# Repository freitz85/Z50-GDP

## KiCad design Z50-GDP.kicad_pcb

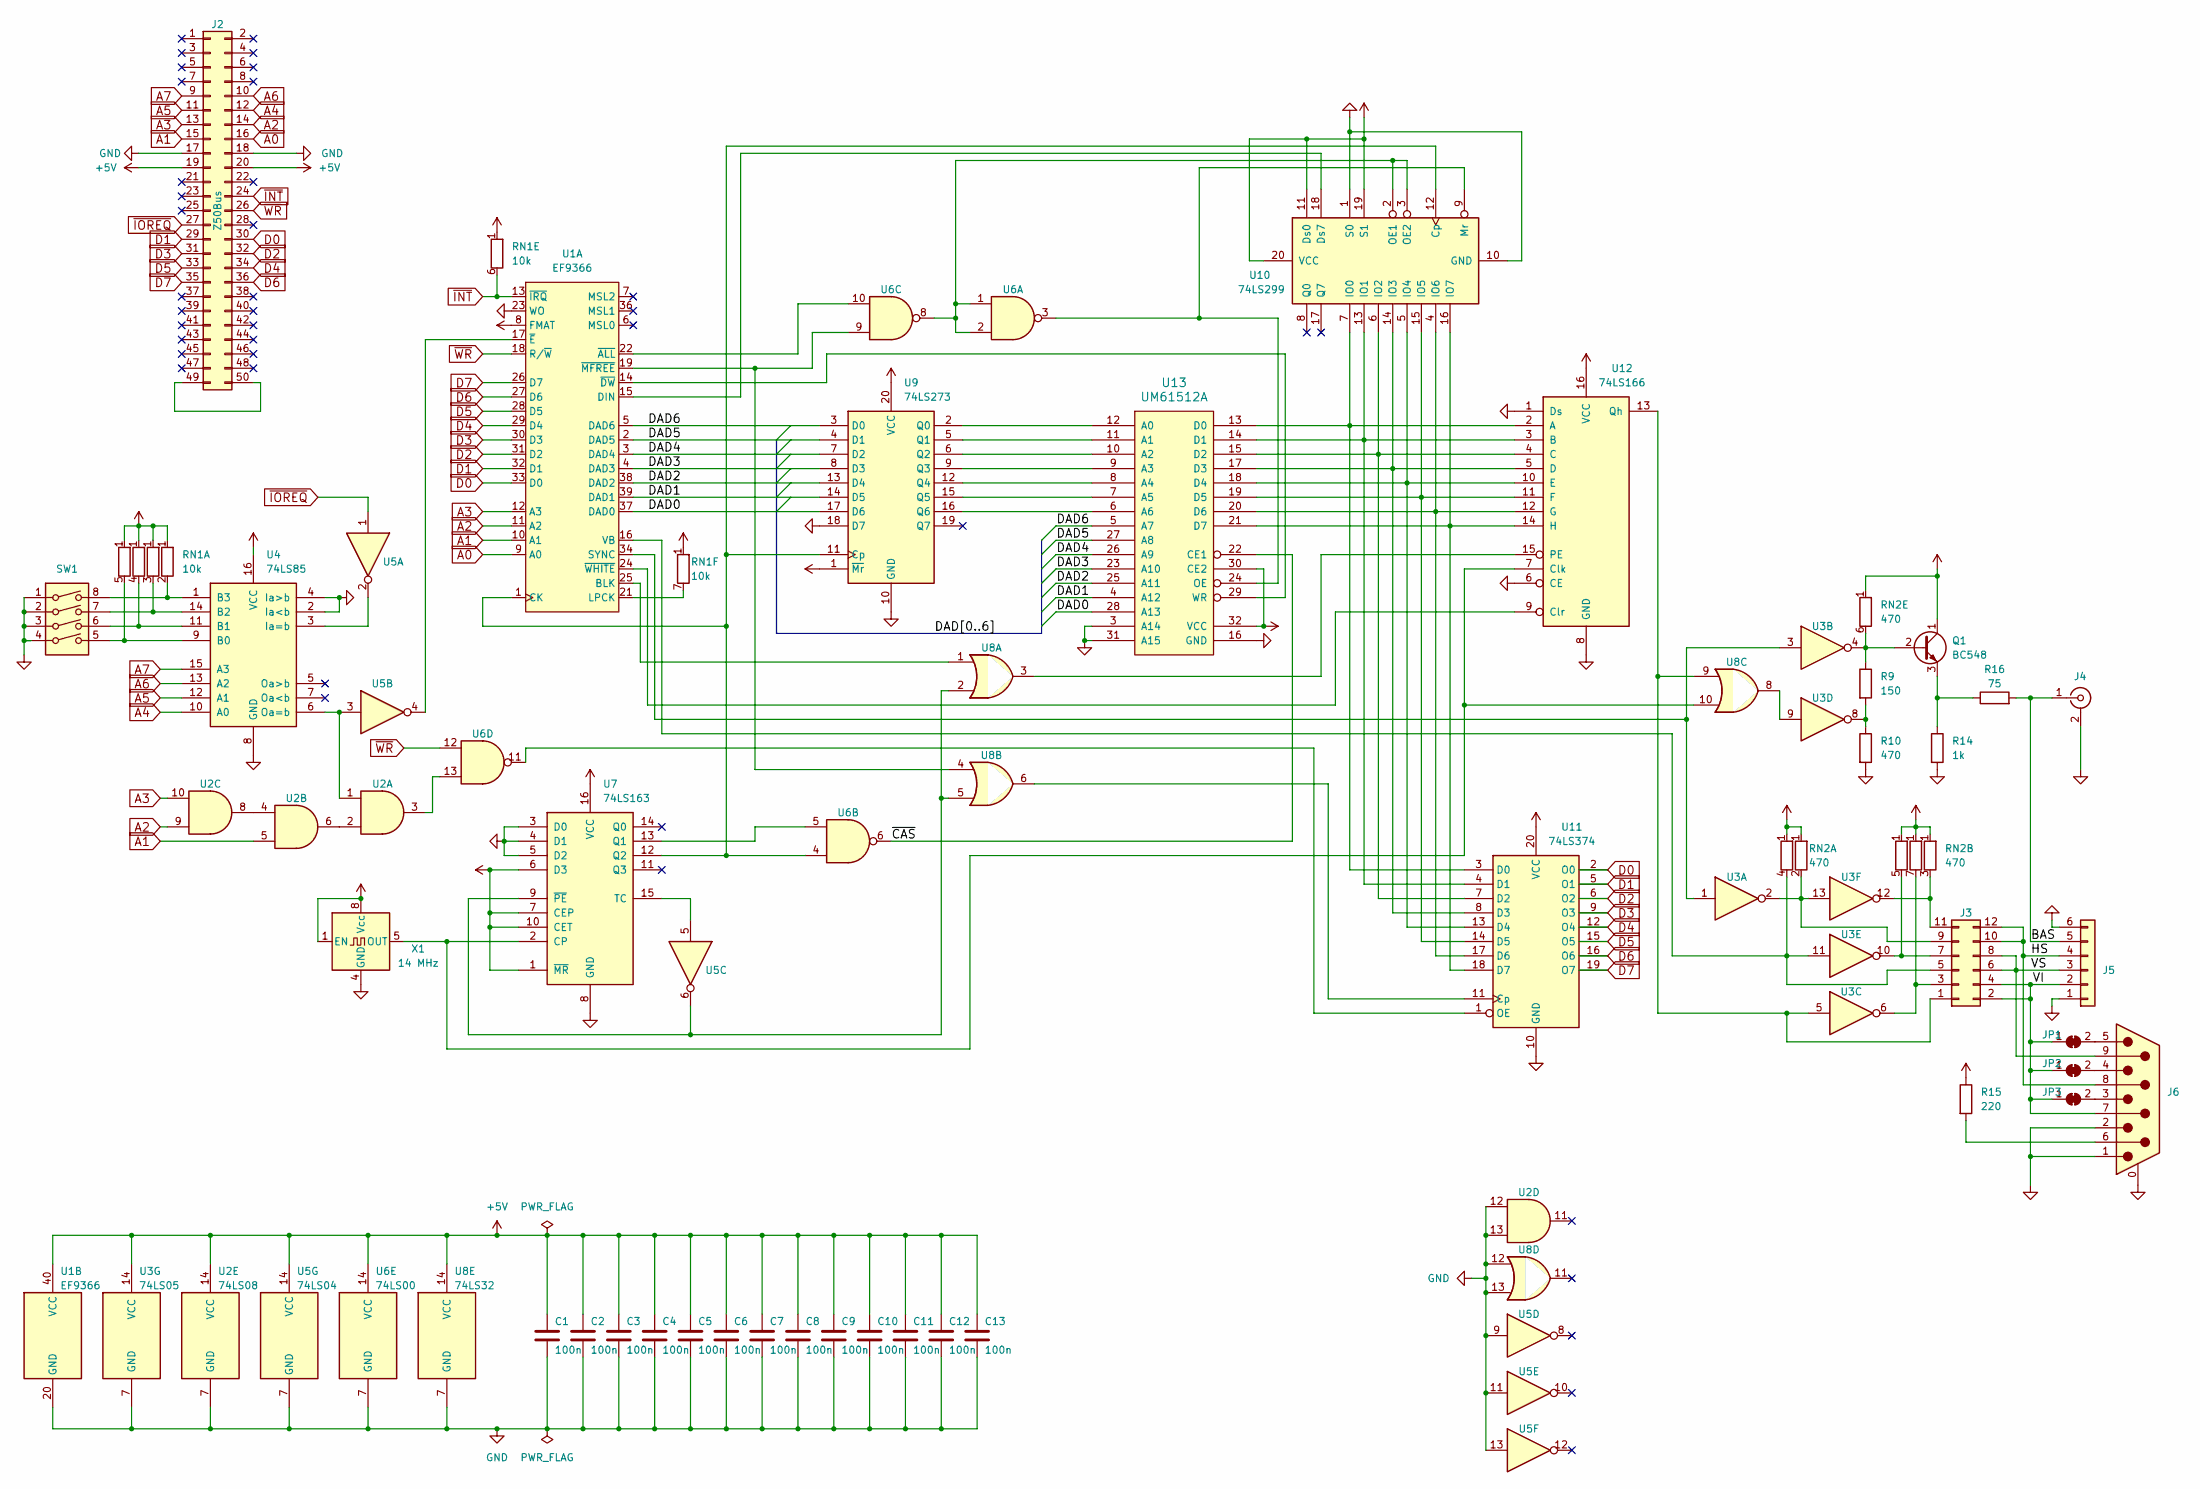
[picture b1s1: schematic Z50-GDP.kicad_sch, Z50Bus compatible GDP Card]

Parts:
C1, C2, C3, C4, C5, C6, C7, C8, C9, C10, C11, C12, C13: 100n; C_Rect_L4.0mm_W2.5mm_P2.50mm
J2: Z50Bus; IDC-Header_2x25_P2.54mm_Horizontal
J3: Conn_02x06_Odd_Even; PinHeader_2x06_P2.54mm_Vertical
J4: Conn_Coaxial; RCA_C160_Horizontal
J5: Conn_01x06; PinHeader_1x06_P2.54mm_Vertical
J6: DE9_Plug_MountingHoles; DSUB-9_Male_Horizontal_P2.77x2.84mm_EdgePinOffset4.94mm_Hou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
JP1, JP2, JP3: SolderJumper_2_Bridged; SolderJumper-2_P1.3mm_Bridged_RoundedPad1.0x1.5mm
Q1: BC548; TO-92_Inline
R9: 150; R_Axial_DIN0207_L6.3mm_D2.5mm_P10.16mm_Horizontal
R10: 470; R_Axial_DIN0207_L6.3mm_D2.5mm_P10.16mm_Horizontal
R14: 1k; R_Axial_DIN0207_L6.3mm_D2.5mm_P10.16mm_Horizontal
R15: 220; R_Axial_DIN0207_L6.3mm_D2.5mm_P10.16mm_Horizontal
R16: 75; R_Axial_DIN0207_L6.3mm_D2.5mm_P10.16mm_Horizontal
RN1: 10k; R_Array_SIP7
RN2: 470; R_Array_SIP7
SW1: SW_DIP_x04; DIP-8_W7.62mm
U1: EF9366; DIP-40_W15.24mm
U2: 74LS08; DIP-14_W7.62mm
U3: 74LS05; DIP-14_W7.62mm
U4: 74LS85; DIP-16_W7.62mm
U5: 74LS04; DIP-14_W7.62mm
U6: 74LS00; DIP-14_W7.62mm
U7: 74LS163; DIP-16_W7.62mm
U8: 74LS32; DIP-14_W7.62mm
U9: 74LS273; DIP-20_W7.62mm
U10: 74LS299; DIP-20_W7.62mm
U11: 74LS374; DIP-20_W7.62mm
U12: 74LS166; DIP-16_W7.62mm
U13: UM61512A; DIP-32_W7.62mm
X1: 14 MHz; Oscillator_DIP-8

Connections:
+5V: C1.1, C2.1, C3.1, C4.1, C5.1, C6.1, C7.1, C8.1, C9.1, C10.1, C11.1, C12.1, C13.1, J2.19, J2.20, Q1.1 (C), R15.1, RN1.1 (R1), RN2.1 (R1), U1.8 (FMAT), U1.40 (VCC), U2.14 (VCC), U3.14 (VCC), U4.16 (VCC), U5.14 (VCC), U6.14 (VCC), U7.1 (~MR), U7.6 (D3), U7.7 (CEP), U7.10 (CET), U7.16 (VCC), U8.14 (VCC), U9.1 (~Mr), U9.20 (VCC), U10.11 (Ds0), U10.19 (S1), U10.20 (VCC), U11.20 (VCC), U12.16 (VCC), U13.30 (CE2), U13.32 (VCC), X1.1 (EN), X1.8 (Vcc)
/BAS: J4.1 (In), J5.5, R16.2
/DAD0: U1.37 (DAD0), U9.17 (D6), U13.28 (A13)
/DAD1: U1.39 (DAD1), U9.14 (D5), U13.4 (A12)
/DAD2: U1.38 (DAD2), U9.13 (D4), U13.25 (A11)
/DAD3: U1.4 (DAD3), U9.8 (D3), U13.23 (A10)
/DAD4: U1.3 (DAD4), U9.7 (D2), U13.26 (A9)
/DAD5: U1.2 (DAD5), U9.4 (D1), U13.27 (A8)
/DAD6: U1.5 (DAD6), U9.3 (D0), U13.5 (A7)
/HS: J3.10, J3.12, J5.4, J6.8
/VI: J3.2, J3.4, J5.2, J6.7, JP1.1 (A), JP2.1 (A), JP3.1 (A)
/VS: J3.6, J3.8, J5.3, J6.9
/~CAS: U6.6, U13.22 (CE1)
A0: J2.16, U1.9 (A0)
A1: J2.15, U1.10 (A1), U2.5
A2: J2.14, U1.11 (A2), U2.9
A3: J2.13, U1.12 (A3), U2.10
A4: J2.12, U4.10 (A0)
A5: J2.11, U4.12 (A1)
A6: J2.10, U4.13 (A2)
A7: J2.9, U4.15 (A3)
D0: J2.30, U1.33 (D0), U11.2 (O0)
D1: J2.29, U1.32 (D1), U11.5 (O1)
D2: J2.32, U1.31 (D2), U11.6 (O2)
D3: J2.31, U1.30 (D3), U11.9 (O3)
D4: J2.34, U1.29 (D4), U11.12 (O4)
D5: J2.33, U1.28 (D5), U11.15 (O5)
D6: J2.36, U1.27 (D6), U11.16 (O6)
D7: J2.35, U1.26 (D7), U11.19 (O7)
GND: C1.2, C2.2, C3.2, C4.2, C5.2, C6.2, C7.2, C8.2, C9.2, C10.2, C11.2, C12.2, C13.2, J2.17, J2.18, J4.2 (Ext), J5.1, J5.6, J6.0 (PAD), J6.1, J6.2, R10.2, R14.2, SW1.1, SW1.2, SW1.3, SW1.4, U1.20 (GND), U1.23 (WO), U2.7 (GND), U2.12, U2.13, U3.7 (GND), U4.2 (Ia<b), U4.4 (Ia>b), U4.8 (GND), U5.7 (GND), U5.9, U5.11, U5.13, U6.7 (GND), U7.3 (D0), U7.4 (D1), U7.5 (D2), U7.8 (GND), U8.7 (GND), U8.12, U8.13, U9.10 (GND), U9.18 (D7), U10.1 (S0), U10.10 (GND), U11.10 (GND), U12.1 (Ds), U12.6 (CE), U12.8 (GND), U13.3 (A14), U13.16 (GND), U13.31 (A15), X1.4 (GND)
unnamed: J2.49, J2.50
unnamed: J3.1, U3.5, U8.9, U12.13 (Qh)
unnamed: J3.3, RN2.7 (R6.2), U3.6
unnamed: J3.5, RN2.4 (R3.2), U1.16 (VB), U3.11
unnamed: J3.7, RN2.5 (R4.2), U3.10
unnamed: J3.9, RN2.2 (R1.2), U3.2, U3.13
unnamed: J3.11, RN2.3 (R2.2), U3.12
unnamed: J6.6, R15.2
unnamed: J6.5, JP1.2 (B)
unnamed: J6.4, JP2.2 (B)
unnamed: J6.3, JP3.2 (B)
unnamed: Q1.2 (B), R9.1, RN2.6 (R5.2), U3.4
unnamed: Q1.3 (E), R14.1, R16.1
unnamed: R9.2, R10.1, U3.8
unnamed: RN1.2 (R1.2), SW1.8, U4.1 (B3)
unnamed: RN1.3 (R2.2), SW1.7, U4.14 (B2)
unnamed: RN1.4 (R3.2), SW1.6, U4.11 (B1)
unnamed: RN1.5 (R4.2), SW1.5, U4.9 (B0)
unnamed: RN1.7 (R6.2), U1.21 (LPCK)
unnamed: U1.25 (BLK), U8.1
unnamed: U1.34 (SYNC), U3.1, U3.3
unnamed: U1.22 (~ALL), U6.10
unnamed: U1.17 (~E), U5.4
unnamed: U1.19 (~MFREE), U6.9, U8.4
unnamed: U2.2, U2.6
unnamed: U2.3, U6.13
unnamed: U2.4, U2.8
unnamed: U3.9, U8.8
unnamed: U4.3 (Ia=b), U5.2
unnamed: U2.1, U4.6 (Oa=b), U5.3
unnamed: U6.5, U7.13 (Q1)
unnamed: U5.5, U7.15 (TC)
unnamed: U5.6, U7.9 (~PE), U8.2, U8.5
unnamed: U1.1 (CK), U6.4, U7.12 (Q2), U9.11 (Cp), U10.12 (Cp)
unnamed: U1.15 (DIN), U10.18 (Ds7)
unnamed: U10.7 (IO0), U11.3 (D0), U12.2 (A), U13.13 (D0)
unnamed: U10.13 (IO1), U11.4 (D1), U12.3 (B), U13.14 (D1)
unnamed: U10.6 (IO2), U11.7 (D2), U12.4 (C), U13.15 (D2)
unnamed: U10.14 (IO3), U11.8 (D3), U12.5 (D), U13.17 (D3)
unnamed: U10.5 (IO4), U11.13 (D4), U12.10 (E), U13.18 (D4)
unnamed: U10.15 (IO5), U11.14 (D5), U12.11 (F), U13.19 (D5)
unnamed: U10.4 (IO6), U11.17 (D6), U12.12 (G), U13.20 (D6)
unnamed: U10.16 (IO7), U11.18 (D7), U12.14 (H), U13.21 (D7)
unnamed: U6.3, U10.9 (Mr), U13.24 (OE)
unnamed: U6.1, U6.2, U6.8, U10.2 (OE1), U10.3 (OE2)
unnamed: U8.6, U11.11 (Cp)
unnamed: U6.11, U11.1 (OE)
unnamed: U7.2 (CP), U8.10, U12.7 (Clk), X1.5 (OUT)
unnamed: U1.24 (~WHITE), U12.9 (Clr)
unnamed: U8.3, U12.15 (PE)
unnamed: U9.2 (Q0), U13.12 (A0)
unnamed: U9.5 (Q1), U13.11 (A1)
unnamed: U9.6 (Q2), U13.10 (A2)
unnamed: U9.9 (Q3), U13.9 (A3)
unnamed: U9.12 (Q4), U13.8 (A4)
unnamed: U9.15 (Q5), U13.7 (A5)
unnamed: U9.16 (Q6), U13.6 (A6)
unnamed: U1.14 (~DW), U13.29 (WR)
~INT: J2.24, RN1.6 (R5.2), U1.13 (~IRQ)
~IOREQ: J2.27, U5.1
~WR: J2.26, U1.18 (R/~W), U6.12

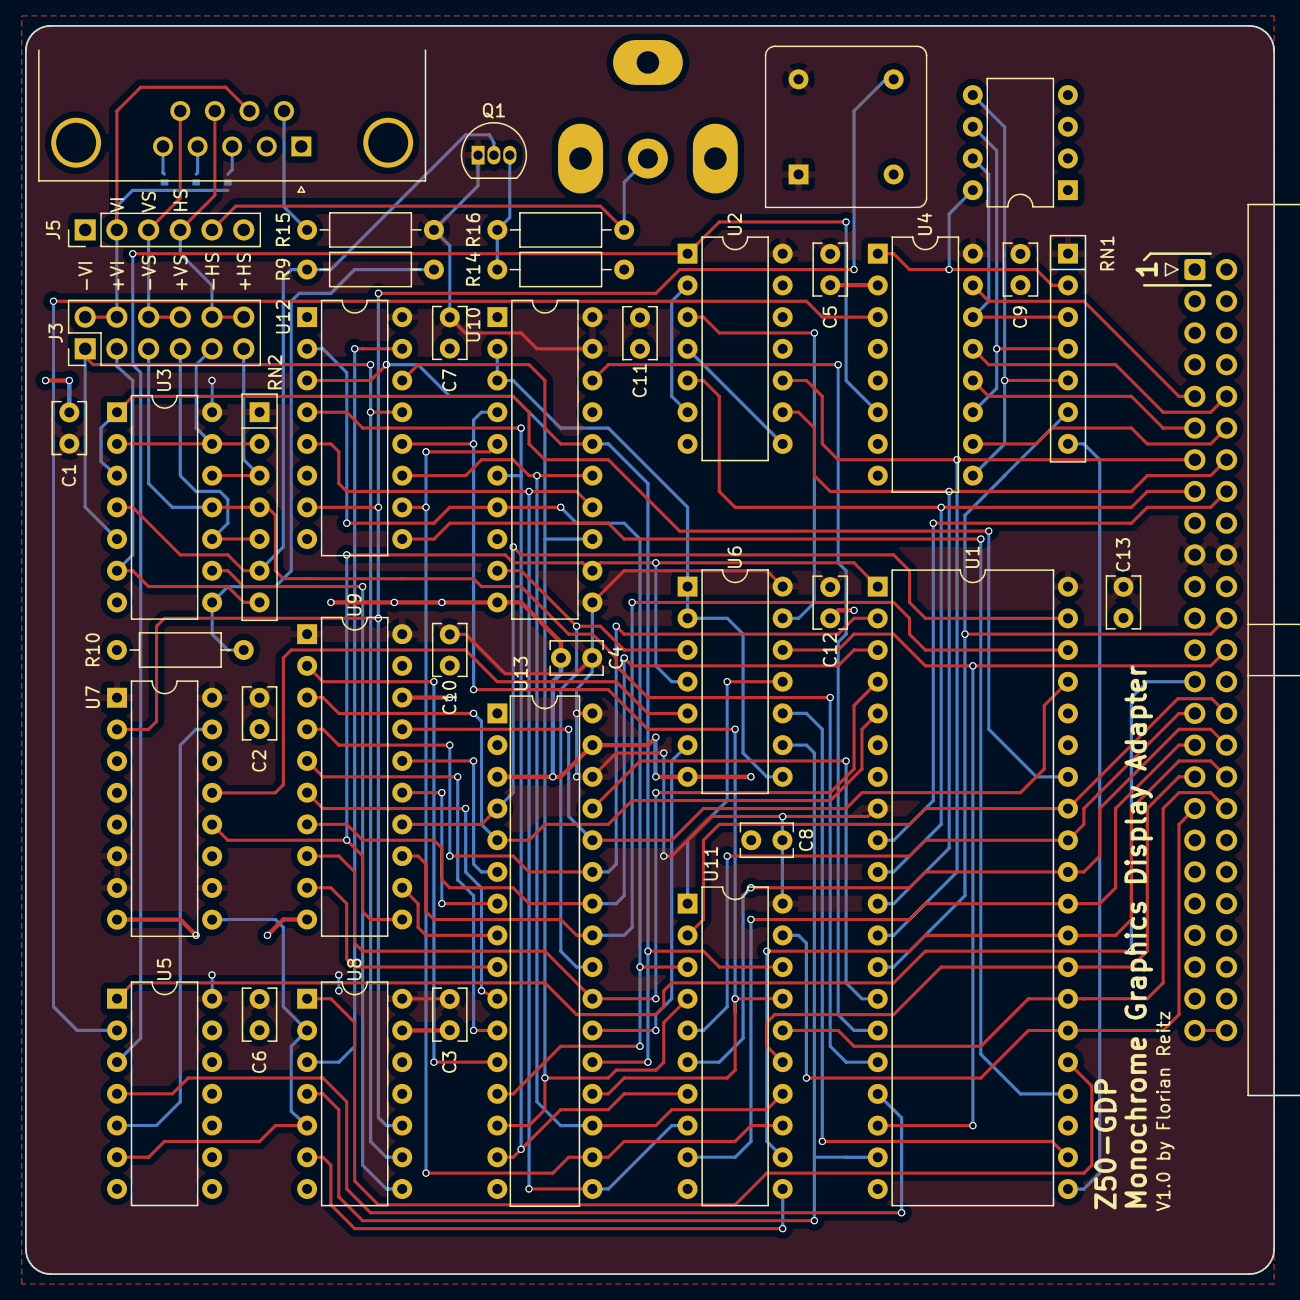
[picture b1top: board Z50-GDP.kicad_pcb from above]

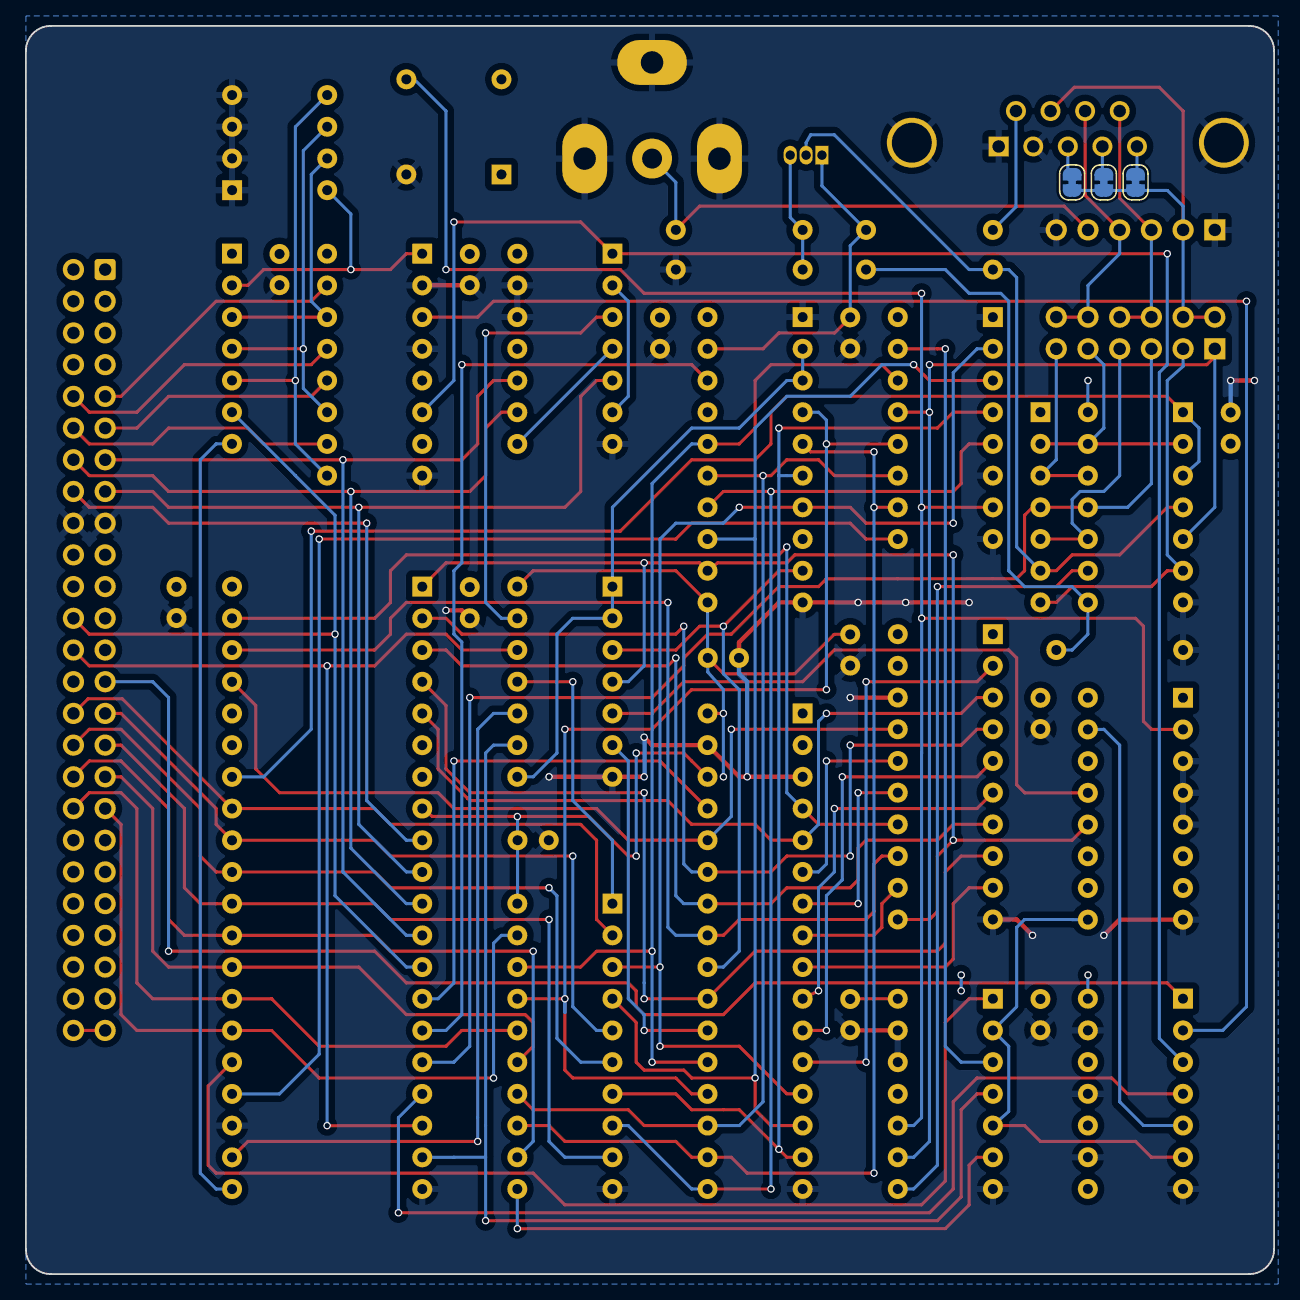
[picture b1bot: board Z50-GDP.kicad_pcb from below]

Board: 2 copper layers, 100.0 x 100.0 mm, 44 parts (3 on the bottom side), 91 nets.

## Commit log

2024-04-28 Files added
2024-04-29 memory-umc added
2024-04-29 Schematic basically ready
2024-04-29 Schematic annotated
2024-05-03 Routing completed
2024-05-03 Silkscreen
2024-05-05 Schematic cleanup
